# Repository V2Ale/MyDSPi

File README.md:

<!DOCTYPE html PUBLIC "-//W3C//DTD HTML 4.01//EN" "http://www.w3.org/TR/html4/strict.dtd">
<html>
<head>
  <meta content="text/html; charset=ISO-8859-1"
 http-equiv="content-type">
  <h1>MyDSPi</h1>
</head>
<body>

<br>
<div style="margin-left: 40px;">MyDSPi is an easy to
implement solution for audio processing and amplification with a
Raspberry Pi (2 and 3) audio output. <br>
It's intended to be a cost effective solution to make
active&nbsp;speakers.<br>
Electronic circuit is based on Analog Device ADAU1701 DSP and Texas
Instrument TPA3118 amplifier.<br>
<br>
More information  avaialble at <a href="http://mydspi;v2ale.com/?utm_source=Github&utm_medium=Link&utm_campaign=mainpage" >mydspi.v2ale.com</a>
<br>
</div>
<br style="font-weight: bold;">
<h3>Hardware description</h3>
<h4 style="margin-left: 40px; width: 1239px;">Overview : </h4>
<div style="margin-left: 40px;"><br>
<div style="margin-left: 40px;">MyDSPi is designed to be
compact and mounted over a Raspberry Pi 2 board. Hardware is split over
2 printed circuit boards stack one above the other.<br><br>
<br>
<br>
The first board is dedicated to DSP processing and Digital to Analog
signal convertion from Raspberry Pi audio output.&nbsp;Audio must
be output from Raspberry
Pi through I2S output pins.<br>
DSP is controlled by Raspberry Pi using I2C&nbsp; interface and
requires no
advanced DSP programming to have signal processed and can be easily
configured by editing a configuration file.<br>
The DSP work at fixed sampling frequency of 48000 Hz. <br>
Output channels are transmitted to the amplifier board through I2S
protocol.<br>
<br>
The second board host Digital to Analog converter that feed the
amplifier with analog signal for amplification. Power supply input
circuit is also located on this PCB, which can accept any supply
voltage from 12 to 24 volts to feed all system power supply (including
the Raspberry Pi).<br>
<br>
For more details about each board, please refer to :<br><br>
<ul>
<li><a href="https://github.com/V2Ale/MyDSPi/tree/master/Electronic/DSP%20Board/2.0">DSP Board page</a></li>
<li><a href="https://github.com/V2Ale/MyDSPi/tree/master/Electronic/Amplification%20Board">Amplifier board page</a></li>
</ul>
</div>
</div>
<br>
<h3><big>Software description</big></h3>
<div style="margin-left: 40px;">Once install is done the
MyDSPi software run at start-up to load default DSP parameters and then
load the parameters read from the configuration file.<br>
<br>
</div>
<h4>DSP Capabilities description</h4>
<br>
<div style="margin-left: 80px;">The default parameters of
the DSP are right now a 2 input / 2
output configuration with a default crossover and no EQ values loaded.
Parameter customization is done throught the MyDSPi.conf file and can
configure : <br>
<br>
<div style="margin-left: 40px;">- Input channels volume
controls<br>
- Input channels mute controls<br>
- 2 channels crossover<br>
- output channels Delay (up to 412 samples) <br>
- Ouput channel mute control<br>
- Ouput channel phase control<br>
- Output channel volume control<br>
</div>
</div>
<br>
<h3>Installation</h3>
Installation of &nbsp;MyDSPi is tested and developped for Linux
Raspbian Jessie distribution.<br>
<br>
The following step describes only the installation major steps. <br>

<ul>
<li>Setup I2C (<a href="https://learn.adafruit.com/adafruits-raspberry-pi-lesson-4-gpio-setup/configuring-i2c">
https://learn.adafruit.com/adafruits-raspberry-pi-lesson-4-gpio-setup/configuring-i2c</a>)<br>
</li>
<li>Setup I2S soundcard (following &nbsp;<a href="https://www.hifiberry.com/build/documentation/hifiberry-software-configuration/">https://www.hifiberry.com/build/documentation/hifiberry-software-configuration/</a>)<br>
</li>
<li>
 Run installation script (see https://github.com/V2Ale/MyDSPi/tree/master/Software/Install)<br>
 </li>
 </ul>

<h3>Configuration</h3>
To edit the configuration file, use the command :<br>
<pre>&nbsp;sudo nano /etc/default/MyDSPi.conf</pre>
For more details about configuration file rules, please refer to <span
 style="color: red;">https://github.com/V2Ale/MyDSPi/tree/master/Software/Install/config</span><br>
<br>
<h3>Roadmap</h3>
Support 5.1 configuration<br>
Support 7.1 configuration<br>
Support quadriphonic configuration<br>
&nbsp;<br>

</body>
</html>

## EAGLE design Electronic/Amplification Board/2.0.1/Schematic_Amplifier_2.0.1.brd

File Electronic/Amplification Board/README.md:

<!DOCTYPE html PUBLIC "-//W3C//DTD HTML 4.01//EN" "http://www.w3.org/TR/html4/strict.dtd">
<html>
<head>
  <meta content="text/html; charset=ISO-8859-1"
 http-equiv="content-type">
</head>
<body>
<h1>Amplifier and Power Supply Board</h1>
<h3>Overview</h3>
<br>
Amplifier and Power Supply board is the second PCB of this project that
can be stack with the DSP board. It's designed to host 2 set of
amplifiers and DAC, which can handle up to for 4 channels of
amplification. In addition, the board is used for power supply the
entire stack. <br>
<br style="color: red;">
<span style="color: red;"></span><br>
<br>
<h3>DAC</h3>
<br>
Digital to Analog conveters used for this board are PCM5102a (and
similar such as PCM5100). The
benefit of using PCM5102 DAC is that it does not requires the I2S
high frequency system clock (SCK) to work making routing between boards
much easier. <br>
Also, this component provides additionnal controls like demphasis, FIR
or IIR filter of output, format (I2S or Left justified) and soft mute.
Those controls are driven by a port expander with I2C interface that
allows end user to use this amplifier board for other designs. More
details on those controls can be found in the component datasheet. <br>
Last, this component
is readily cheap and available on the market (PCM5100 being pin to pin
compatible).<br>
<br>
<br>
<h3>Amplifier</h3>
&nbsp;<br>
The Texas Instrument TPA3118 amplifiers are stereo class D amplifiers
that can drive 2x30W into 8 Ohms load (with a 24V supply). It can
operate with a wide single operating voltage from 4.5V to 26V keeping
the power supply design simple. <br>
As audio input, the amplifier expect single ended audio which are
provided by DAC. All external controls (like gain) of the amplifier are
set constant except the amplifier mute which can be controlled thanks
to the port expander.<br>
Last, the amplifier integrates bad operating conditions (like
overtemperature, output short circuit) which are sent back to the
Faultz pins. Those pins are connected to the port expander and can be
monitored as well.<br>
<br>
<h3>Port Expander</h3>
<br>
As explain in previous parts, the port expander is in charge of
monitoring amplifier state and set DAC and amplifiers controls. The
part used for this task is very common MCP23008 from Microchip.<br>
<br>
<h3>Power Supply </h3>
<br>
The board do not have any power supply transformer and switch mode
power supply block design is outside the scope of this project. As a
result, a maximum of 26V voltage is expected at the DC jack terminal
connector. This voltage is directly used to feed the amplifiers and is
also converted down to a 5V supply voltage for all other boards
(including Raspberry Pi supply). &nbsp; <br>
<br>
<h3>Connectors </h3>
<br>
The&nbsp; 40 pin connector is used to connected to the DSP board
and get DSP output channels,&nbsp; I2C and amplifier mute command.
It also provides the supply rail voltage for the entire project.<br>
<br>
<span style="color: red;">[IMAGE DU SCHEMA DU CONNETEUR]</span><br>
<br>
<table style="text-align: left; width: 378px; height: 1216px;"
 border="1" cellpadding="2" cellspacing="2">
  <tbody>
    <tr>
      <td>Pin</td>
      <td>Name &nbsp; &nbsp; </td>
      <td>Description &nbsp; &nbsp; &nbsp; &nbsp;
&nbsp;</td>
    </tr>
    <tr>
      <td>1</td>
      <td>DC In</td>
      <td>Input Power supply is duplicated on this pin</td>
    </tr>
    <tr>
      <td>2</td>
      <td>DC In</td>
      <td>Input Power supply is duplicated on this pin</td>
    </tr>
    <tr>
      <td>3</td>
      <td>-</td>
      <td>Not used</td>
    </tr>
    <tr>
      <td>4</td>
      <td>SCL</td>
      <td>I2C Clock</td>
    </tr>
    <tr>
      <td>5</td>
      <td>-</td>
      <td>Not used</td>
    </tr>
    <tr>
      <td>6</td>
      <td>SDA</td>
      <td>I2C Data</td>
    </tr>
    <tr>
      <td>7</td>
      <td>Amp_mute</td>
      <td>Pin connected to Raspberry pi and amplifier mute pin.</td>
    </tr>
    <tr>
      <td>8</td>
      <td>-</td>
      <td>Not used</td>
    </tr>
    <tr>
      <td>9</td>
      <td>-</td>
      <td>Not used</td>
    </tr>
    <tr>
      <td>10</td>
      <td>-</td>
      <td>Not used</td>
    </tr>
    <tr>
      <td>11</td>
      <td>GND</td>
      <td>Ground</td>
    </tr>
    <tr>
      <td>12</td>
      <td>-</td>
      <td>Not used</td>
    </tr>
    <tr>
      <td>13</td>
      <td>-</td>
      <td>Not used</td>
    </tr>
    <tr>
      <td>14</td>
      <td>-</td>
      <td>Not used</td>
    </tr>
    <tr>
      <td>15</td>
      <td>-</td>
      <td>Not used</td>
    </tr>
    <tr>
      <td>16</td>
      <td>-</td>
      <td>Not used</td>
    </tr>
    <tr>
      <td>17</td>
      <td>GPO3</td>
      <td>DSP MPIO3 Output pin</td>
    </tr>
    <tr>
      <td>18</td>
      <td>GPO2</td>
      <td>DSP&nbsp;MPIO2 Output pin</td>
    </tr>
    <tr>
      <td>19</td>
      <td>GPO1</td>
      <td>DSP&nbsp;MPIO1 Output pin</td>
    </tr>
    <tr>
      <td>20</td>
      <td>DSPIN_SADATA0</td>
      <td>DSP I2S input pin 1</td>
    </tr>
    <tr>
      <td>21</td>
      <td>DSP_SDATA0</td>
      <td>DSP I2S output pin 1</td>
    </tr>
    <tr>
      <td>22</td>
      <td>DSP_BCK</td>
      <td>DSP I2S Bitclock output</td>
    </tr>
    <tr>
      <td>23</td>
      <td>DSP_SDATA1</td>
      <td>DSP I2S output pin 2</td>
    </tr>
    <tr>
      <td>24</td>
      <td>DSP_LRCK</td>
      <td>DSP I2S Bitclock output</td>
    </tr>
    <tr>
      <td>25</td>
      <td>ANALOG_IN_R</td>
      <td>DSP Analog input pin 1</td>
    </tr>
    <tr>
      <td>26</td>
      <td>ANALOG_IN_L</td>
      <td>DSP Analog input pin 2</td>
    </tr>
    <tr>
      <td>27</td>
      <td>AUDIO_OUT0</td>
      <td>DSP Analog output 1</td>
    </tr>
    <tr>
      <td>28</td>
      <td>GPO9</td>
      <td>DSP MPIO 9</td>
    </tr>
    <tr>
      <td>29</td>
      <td>AUDIO_OUT1</td>
      <td>DSP Analog output 2</td>
    </tr>
    <tr>
      <td>30</td>
      <td>GPO8</td>
      <td>DSP MPIO 8</td>
    </tr>
    <tr>
      <td>31</td>
      <td>AUDIO_OUT2</td>
      <td>DSP Analog output 3</td>
    </tr>
    <tr>
      <td>32</td>
      <td>AUDIO_OUT3</td>
      <td>DSP Analog output 4</td>
    </tr>
    <tr>
      <td>33</td>
      <td>-</td>
      <td>Not used</td>
    </tr>
    <tr>
      <td>34</td>
      <td>-</td>
      <td>Not used</td>
    </tr>
    <tr>
      <td>35</td>
      <td>GND</td>
      <td>Ground</td>
    </tr>
    <tr>
      <td>36</td>
      <td>GND</td>
      <td>Ground</td>
    </tr>
    <tr>
      <td>37</td>
      <td>5V</td>
      <td>5V power supply</td>
    </tr>
    <tr>
      <td>38</td>
      <td>GND</td>
      <td>Ground</td>
    </tr>
    <tr>
      <td>39</td>
      <td>5V</td>
      <td>5V power supply</td>
    </tr>
    <tr>
      <td>40</td>
      <td>5V</td>
      <td>5V power supply</td>
    </tr>
  </tbody>
</table>
<br>
<br>
</body>
</html>

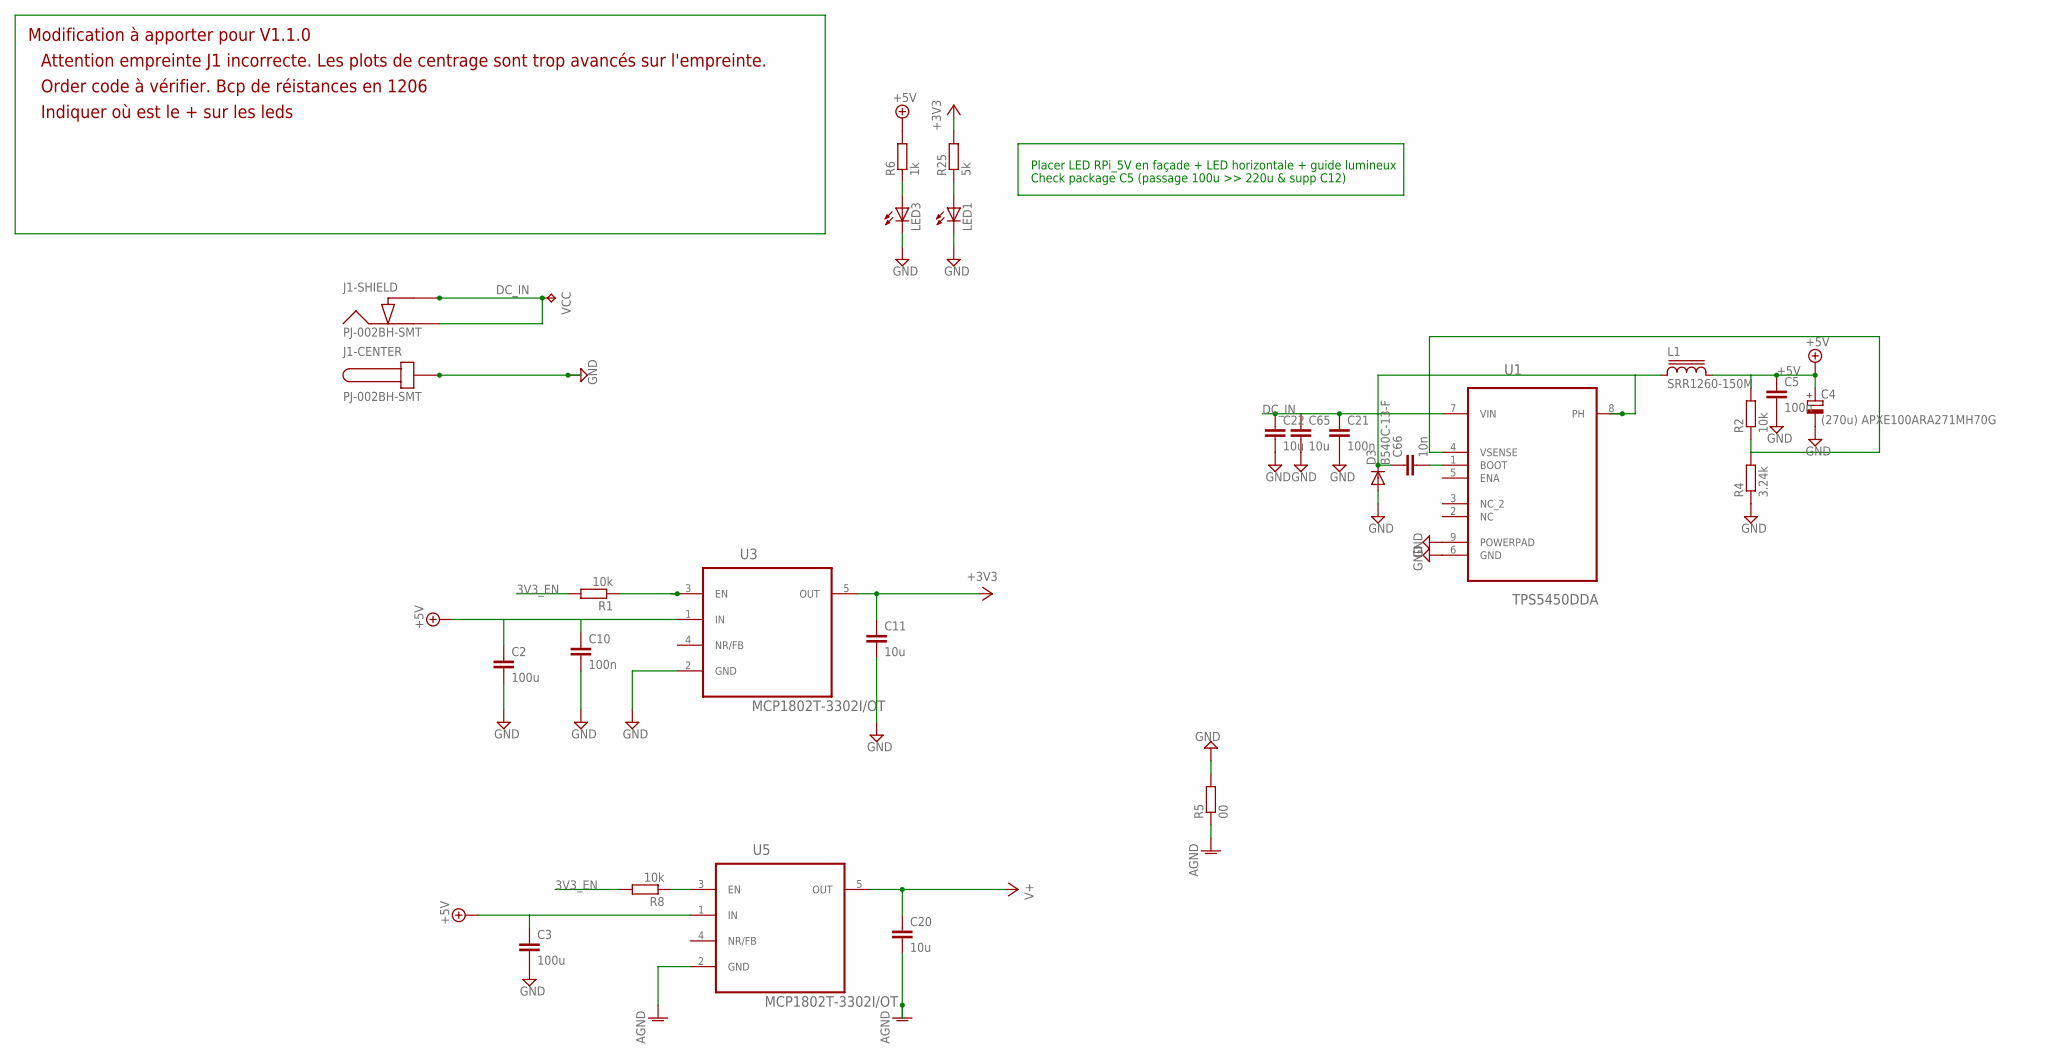
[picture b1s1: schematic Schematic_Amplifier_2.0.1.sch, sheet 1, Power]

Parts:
C2, C3: 100u; C1206
C4: (270u) APXE100ARA271MH70G; 175TMP-0810
C5, C10, C21: 100n; C0603
C11, C20, C22, C65: 10u; C0805
C66: 10n; C0603
D3: B540C-13-F; SMC
J1: PJ-002BH-SMT; 002BH-SMT
L1: SRR1260-150M; SRR1280
LED1: LEDSML0603; SML0603
LED3: LEDSML1206; SML1206
R1, R2, R8: 10k; R0603
R4: 3.24k; R0603
R5: 00; R0603
R6: 1k; R0603
R25: 5k; R0603
U1: TPS5450DDA; SOIC127P600X170-9N
U3, U5: MCP1802T-3302I/OT; SOT95P280X145-5N
VCC: TPTP20R; TP20R

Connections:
3V3_EN: R1.2, R8.2; also elsewhere on the board
+3V3: C11.1, R25.2, U3.5 (OUT); also elsewhere on the board
+5V: C2.1, C3.1, C4.+, C5.1, C10.1, L1.2, R2.2, R6.2, U3.1 (IN), U5.1 (IN); also elsewhere on the board
AGND: C20.2, R5.1, U5.2 (GND); also elsewhere on the board
DC_IN: C21.1, C22.1, C65.1, J1.2, J1.3, U1.7 (VIN), VCC.TP; also elsewhere on the board
GND: C2.2, C3.2, C4.-, C5.2, C10.2, C11.2, C21.2, C22.2, C65.2, D3.A, J1.CENTER1 (1), J1.CENTER2 (1), LED1.C, LED3.C, R4.1, R5.2, U1.6 (GND), U1.9 (POWERPAD), U3.2 (GND); also elsewhere on the board
unnamed: R1.1, U3.3 (EN)
unnamed: LED1.A, R25.1
unnamed: C66.2, U1.1 (BOOT)
unnamed: LED3.A, R6.1
unnamed: R8.1, U5.3 (EN)
unnamed: C66.1, D3.C, L1.1, U1.8 (PH)
unnamed: R2.1, R4.2, U1.4 (VSENSE)
V+: C20.1, U5.5 (OUT); also elsewhere on the board

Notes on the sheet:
Placer LED RPi_5V en façade + LED horizontale + guide lumineux
Check package C5 (passage 100u >> 220u & supp C12)
Attention empreinte J1 incorrecte. Les plots de centrage sont trop avancés sur l'empreinte.
Modification à apporter pour V1.1.0
Order code à vérifier. Bcp de réistances en 1206
Indiquer où est le + sur les leds

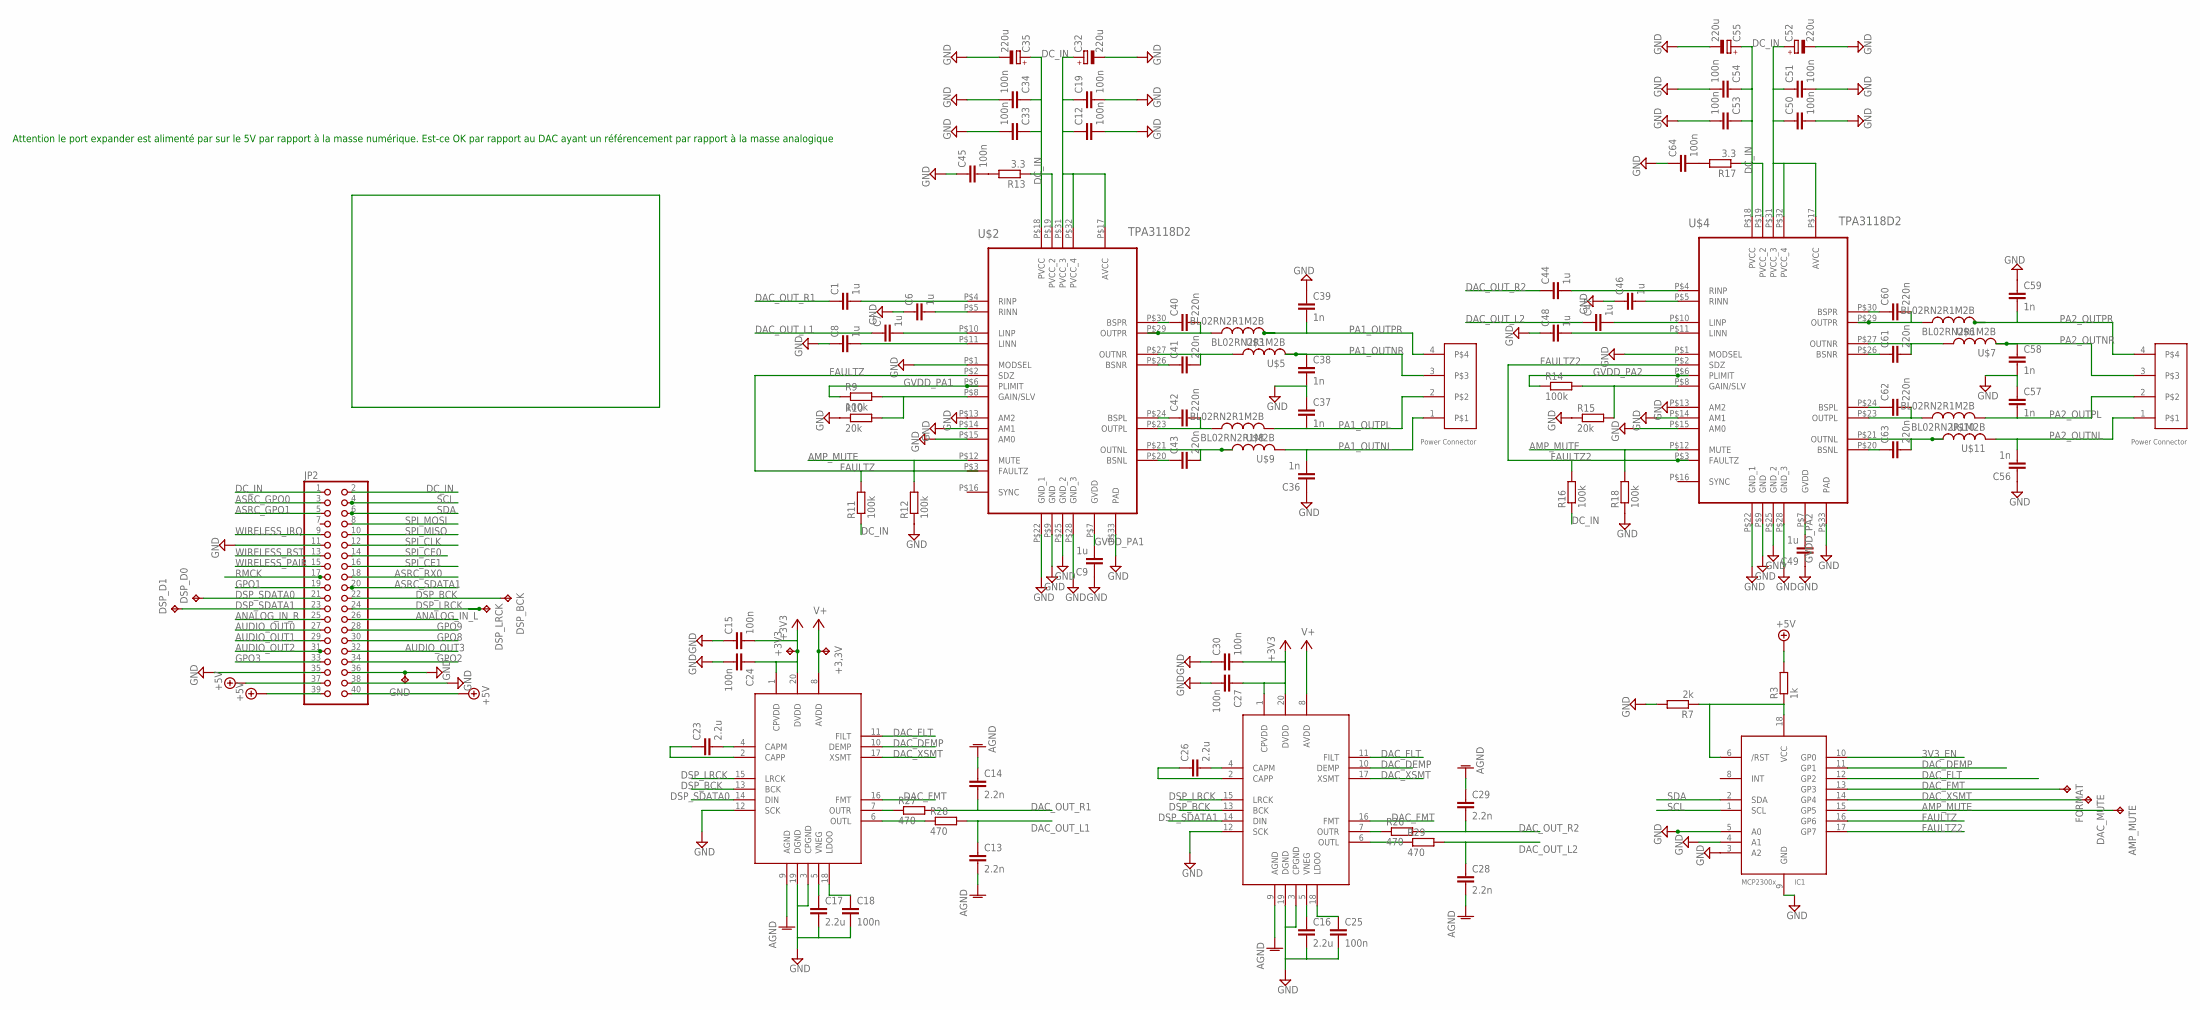
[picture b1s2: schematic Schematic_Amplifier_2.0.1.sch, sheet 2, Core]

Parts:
+3,3V, +3V3: TPTP10R; TP10R
AMP_MUTE: TPTP08R; TP08R
C1, C6, C7, C8, C9, C44, C46, C47, C48, C49: 1u; C0603
C12, C15, C18, C19, C24, C25, C27, C30, C33, C34, C45, C50, C51, C53, C54, C64: 100n; C0603
C13, C14, C28, C29: 2.2n; C0603
C16, C17, C23, C26: 2.2u; C0603
C32, C35, C52, C55: 220u; E2,5-6
C36, C37, C38, C39, C56, C57, C58, C59: 1n; C0603
C40, C41, C42, C43, C60, C61, C62, C63: 220n; C0603
DAC0, DAC1: PCM5102A; 20L-TSSOP
DAC_MUTE: TPTP08R; TP08R
DSP_BCK: TPTP08R; TP08R
DSP_D0, DSP_D1: TPTP08R; TP08R
DSP_LRCK: TPTP08R; TP08R
FORMAT: TPTP08R; TP08R
GND: TPTP19SQ; TP19SQ
IC1: MCP23008/SO; SO18W
JP2: PINHD-2X20; 2X20
R3: 1k; R0603
R7: 2k; R0603
R9, R11, R12, R14, R16, R18: 100k; R0603
R10, R15: 20k; R0603
R13, R17: 3.3; R0603
R26, R27, R28, R29: 470; R0603
U$1, U$12: 1-1123723-4; POWER_CON_HEADER
U$2, U$4: TPA3118D2; TSSOP32
U$3, U$5, U$6, U$7, U$8, U$9, U$10, U$11: BL02RN2R1M2B; FB

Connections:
3V3_EN: IC1.10 (GP0); also elsewhere on the board
$OUTR: DAC0.7 (OUTR), R26.1
+3V3: +3V3.TP, C15.2, C24.1, C27.1, C30.2, DAC0.1 (CPVDD), DAC0.20 (DVDD), DAC1.1 (CPVDD), DAC1.20 (DVDD); also elsewhere on the board
+5V: JP2.37, JP2.39, JP2.40, R3.2; also elsewhere on the board
AGND: C13.2, C14.1, C28.2, C29.1, DAC0.9 (AGND), DAC1.9 (AGND); also elsewhere on the board
AMP_MUTE: AMP_MUTE.TP, IC1.15 (GP5), R12.2, R18.2, U$2.P$12 (MUTE), U$4.P$12 (MUTE)
ANALOG_IN_L: JP2.26
ANALOG_IN_R: JP2.25
ASRC_GPO0: JP2.3
ASRC_GPO1: JP2.5
ASRC_RX0: JP2.18
ASRC_SDATA1: JP2.20
AUDIO_OUT0: JP2.27
AUDIO_OUT1: JP2.29
AUDIO_OUT2: JP2.31
AUDIO_OUT3: JP2.32
DAC_DEMP: DAC0.10 (DEMP), DAC1.10 (DEMP), IC1.11 (GP1)
DAC_FLT: DAC0.11 (FILT), DAC1.11 (FILT), IC1.12 (GP2)
DAC_FMT: DAC0.16 (FMT), DAC1.16 (FMT), FORMAT.TP, IC1.13 (GP3)
DAC_OUT_L1: C7.1, C13.1, R28.2
DAC_OUT_L2: C28.1, C47.1, R29.2
DAC_OUT_R1: C1.1, C14.2, R27.2
DAC_OUT_R2: C29.2, C44.1, R26.2
DAC_XSMT: DAC0.17 (XSMT), DAC1.17 (XSMT), DAC_MUTE.TP, IC1.14 (GP4)
DC_IN: C12.1, C19.1, C32.+, C33.1, C34.1, C35.+, C50.1, C51.1, C52.+, C53.1, C54.1, C55.+, JP2.1, JP2.2, R11.1, R13.1, R16.1, R17.1, U$2.P$17 (AVCC), U$2.P$18 (PVCC), U$2.P$31 (PVCC_3), U$2.P$32 (PVCC_4), U$4.P$17 (AVCC), U$4.P$18 (PVCC), U$4.P$31 (PVCC_3), U$4.P$32 (PVCC_4); also elsewhere on the board
DSP_BCK: DAC0.13 (BCK), DAC1.13 (BCK), DSP_BCK.TP, JP2.22
DSP_LRCK: DAC0.15 (LRCK), DAC1.15 (LRCK), DSP_LRCK.TP, JP2.24
DSP_SDATA0: DAC1.14 (DIN), DSP_D0.TP, JP2.21
DSP_SDATA1: DAC0.14 (DIN), DSP_D1.TP, JP2.23
FAULTZ: IC1.16 (GP6), R11.2, U$2.P$2 (SDZ), U$2.P$3 (FAULTZ)
FAULTZ2: IC1.17 (GP7), R16.2, U$4.P$2 (SDZ), U$4.P$3 (FAULTZ)
GND: C6.1, C8.1, C9.1, C12.2, C15.1, C16.2, C17.2, C18.2, C19.2, C24.2, C25.2, C27.2, C30.1, C32.-, C33.2, C34.2, C35.-, C36.1, C37.1, C38.2, C39.1, C45.1, C46.1, C48.1, C49.1, C50.2, C51.2, C52.-, C53.2, C54.2, C55.-, C56.1, C57.1, C58.2, C59.1, C64.1, DAC0.3 (CPGND), DAC0.12 (SCK), DAC0.19 (DGND), DAC1.3 (CPGND), DAC1.12 (SCK), DAC1.19 (DGND), GND.TP, IC1.3 (A2), IC1.4 (A1), IC1.5 (A0), IC1.9 (GND), JP2.11, JP2.35, JP2.36, JP2.38, R7.2, R10.1, R12.1, R15.1, R18.1, U$2.P$1 (MODSEL), U$2.P$9 (GND), U$2.P$13 (AM2), U$2.P$14 (AM1), U$2.P$15 (AM0), U$2.P$22 (GND_1), U$2.P$25 (GND_2), U$2.P$28 (GND_3), U$2.P$33 (PAD), U$4.P$1 (MODSEL), U$4.P$9 (GND), U$4.P$13 (AM2), U$4.P$14 (AM1), U$4.P$15 (AM0), U$4.P$22 (GND_1), U$4.P$25 (GND_2), U$4.P$28 (GND_3), U$4.P$33 (PAD); also elsewhere on the board
GPO1: JP2.19
GPO2: JP2.34
GPO3: JP2.33
GPO8: JP2.30
GPO9: JP2.28
GVDD_PA1: C9.2, R9.1, U$2.P$6 (PLIMIT), U$2.P$7 (GVDD)
GVDD_PA2: C49.2, R14.1, U$4.P$6 (PLIMIT), U$4.P$7 (GVDD)
unnamed: C1.2, U$2.P$4 (RINP)
unnamed: IC1.6 (/RST), IC1.18 (VCC), R3.1, R7.1
unnamed: C6.2, U$2.P$5 (RINN)
unnamed: C7.2, U$2.P$10 (LINP)
unnamed: C8.2, U$2.P$11 (LINN)
unnamed: R9.2, R10.2, U$2.P$8 (GAIN/SLV)
unnamed: C41.2, U$2.P$27 (OUTNR), U$5.P$1 (1)
unnamed: C40.2, U$2.P$29 (OUTPR), U$3.P$1 (1)
unnamed: C42.2, U$2.P$23 (OUTPL), U$8.P$1 (1)
unnamed: C43.2, U$2.P$21 (OUTNL), U$9.P$1 (1)
unnamed: C44.2, U$4.P$4 (RINP)
unnamed: C40.1, U$2.P$30 (BSPR)
unnamed: C17.1, DAC1.5 (VNEG)
unnamed: C23.2, DAC1.4 (CAPM)
unnamed: C45.2, R13.2
unnamed: C46.2, U$4.P$5 (RINN)
unnamed: C47.2, U$4.P$10 (LINP)
unnamed: C41.1, U$2.P$26 (BSNR)
unnamed: C42.1, U$2.P$24 (BSPL)
unnamed: C43.1, U$2.P$20 (BSNL)
unnamed: C48.2, U$4.P$11 (LINN)
unnamed: DAC1.7 (OUTR), R27.1
unnamed: DAC1.6 (OUTL), R28.1
unnamed: C16.1, DAC0.5 (VNEG)
unnamed: C25.1, DAC0.18 (LDOO)
unnamed: C26.2, DAC0.4 (CAPM)
unnamed: C18.1, DAC1.18 (LDOO)
unnamed: C26.1, DAC0.2 (CAPP)
unnamed: R14.2, R15.2, U$4.P$8 (GAIN/SLV)
unnamed: C23.1, DAC1.2 (CAPP)
unnamed: DAC0.6 (OUTL), R29.1
unnamed: C61.2, U$4.P$27 (OUTNR), U$7.P$1 (1)
unnamed: C60.2, U$4.P$29 (OUTPR), U$6.P$1 (1)
unnamed: C62.2, U$4.P$23 (OUTPL), U$10.P$1 (1)
unnamed: C63.2, U$4.P$21 (OUTNL), U$11.P$1 (1)
unnamed: C60.1, U$4.P$30 (BSPR)
unnamed: C61.1, U$4.P$26 (BSNR)
unnamed: C62.1, U$4.P$24 (BSPL)
unnamed: C63.1, U$4.P$20 (BSNL)
unnamed: C64.2, R17.2
PA1_OUTNL: C36.2, U$1.1, U$9.P$2 (2)
PA1_OUTNR: C38.1, U$1.3, U$5.P$2 (2)
PA1_OUTPL: C37.2, U$1.2, U$8.P$2 (2)
PA1_OUTPR: C39.2, U$1.4, U$3.P$2 (2)
PA2_OUTNL: C56.2, U$11.P$2 (2), U$12.1
PA2_OUTNR: C58.1, U$7.P$2 (2), U$12.3
PA2_OUTPL: C57.2, U$10.P$2 (2), U$12.2
PA2_OUTPR: C59.2, U$6.P$2 (2), U$12.4
RMCK: JP2.17
SCL: IC1.1 (SCL), JP2.4
SDA: IC1.2 (SDA), JP2.6
SPI_CE0: JP2.14
SPI_CE1: JP2.16
SPI_CLK: JP2.12
SPI_MISO: JP2.10
SPI_MOSI: JP2.8
V+: +3,3V.TP, DAC0.8 (AVDD), DAC1.8 (AVDD); also elsewhere on the board
WIRELESS_IRQ: JP2.9
WIRELESS_PAIR: JP2.15
WIRELESS_RST: JP2.13

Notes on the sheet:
Attention le port expander est alimenté par sur le 5V par rapport à la masse numérique. Est-ce OK par rapport au DAC ayant un référencement par rapport à la masse analogique

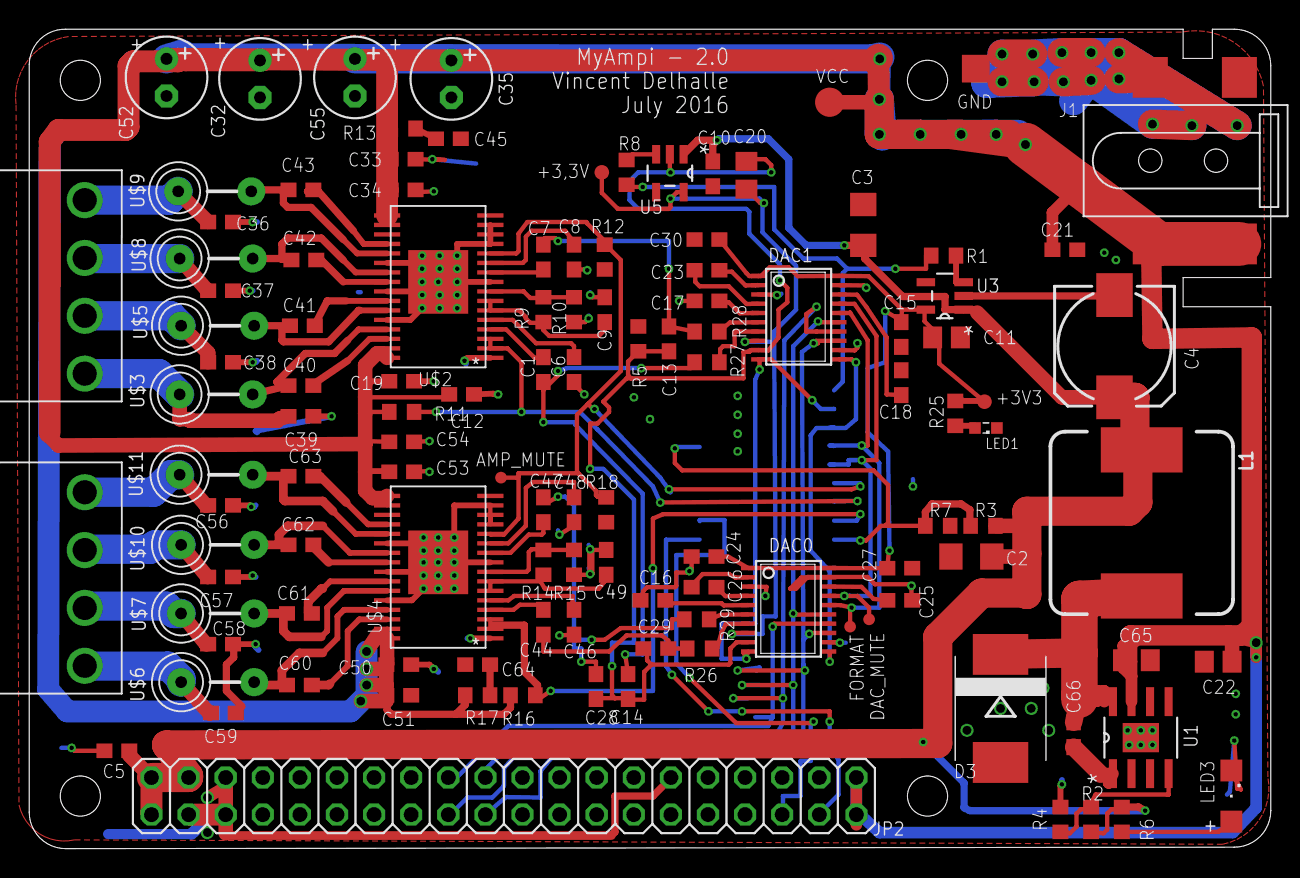
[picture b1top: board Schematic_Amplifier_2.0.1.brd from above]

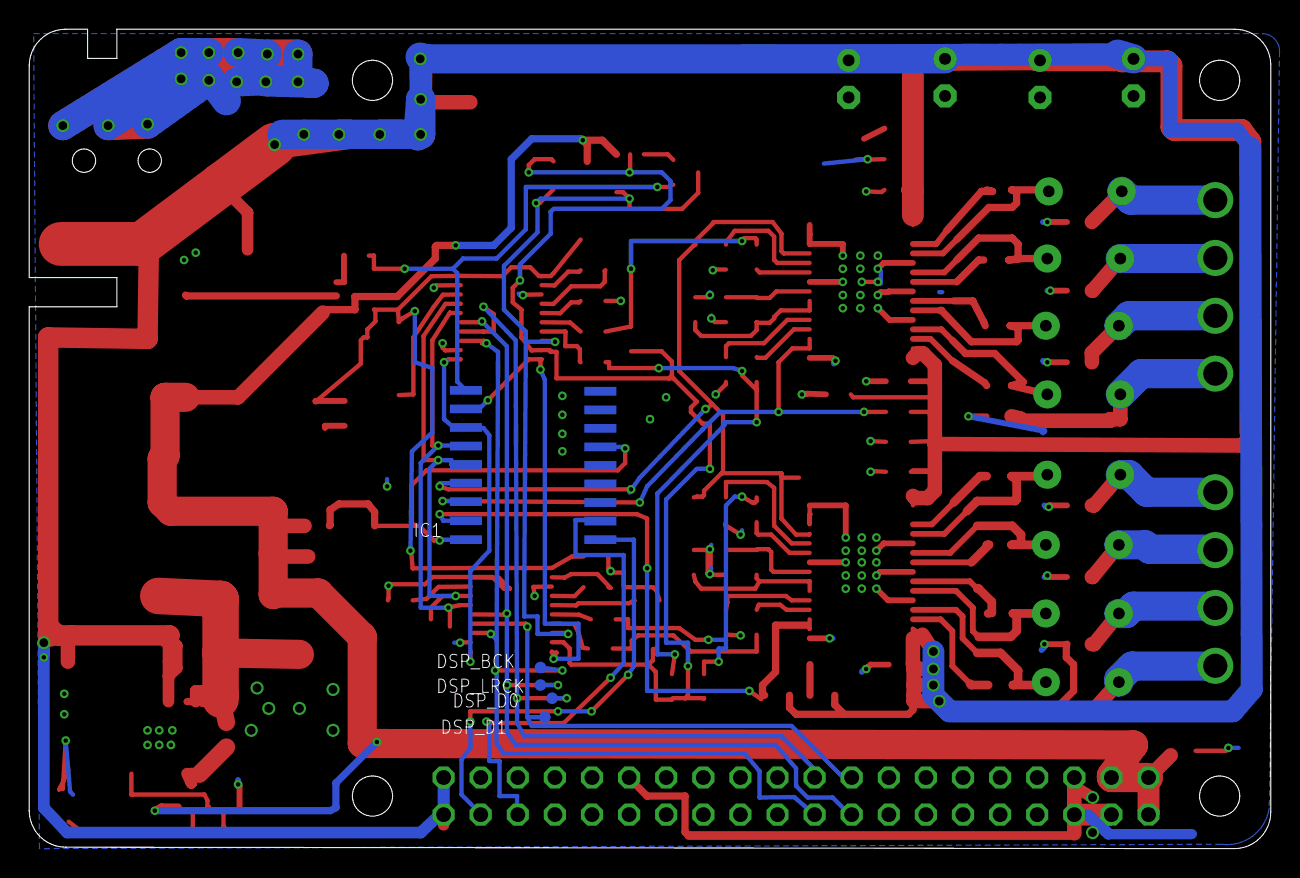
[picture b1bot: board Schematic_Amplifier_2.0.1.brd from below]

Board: 2 copper layers, 85.0 x 56.1 mm, 123 parts (5 on the bottom side), 82 nets.

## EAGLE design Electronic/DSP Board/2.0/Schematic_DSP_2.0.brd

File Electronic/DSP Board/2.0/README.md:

<!DOCTYPE html PUBLIC "-//W3C//DTD HTML 4.01//EN" "http://www.w3.org/TR/html4/strict.dtd">
<html>
<head>
  <meta content="text/html; charset=ISO-8859-1"
 http-equiv="content-type">
</head>
<body>
<h1>DSP PCB</h1>
<h3>Overview</h3>

The DSP used for this project is Analog Device's ADAU1701. It has many
input and output pins, either analog and digital. In the project scope,
this board in 2.0 version is limited to the use of 2 input to 8 digital
and 4 analog outputs.
<br>
It has two 40 pins connectors. One to connect this board to the
raspberry pi, the other to connect the board to other stages (like
amplifier &amp; power supply). The DSP clock is supplied by a
24.576 Mhz Quartz and the programming of the DSP is done via external
microcontroller (Raspberry Pi) using I2C interface.
<br><br>

<h3>Input channels</h3>
The DSP can process analog or digital (I2S) input, but only analog
input can be used. Despite the presence of analog input circuit
components routed in the 40 pin connecor, the project do not rely on
it. <br>
To use the board with the Raspberry Pi, the 3 wires of I2S are
converted by a DAC (PCM5102a) and provided to DSP by the analog input. <br>
The benefit of using PCM5102 DAC is that it does not requires the I2S
system clock (SCK) to work. It's especially useful because the
raspberry pi does not provide the SCK out of the box and it avoids
useless painful struggle with the kernel. <br>
Moreover, this component is readily cheap and available on the market
(PCM5100 being pin to pin compatible). Extra functionality of this DAC
such as filter type or soft mute are not used and not left to end user.<br>

<h3>Output channels</h3>
The DSP can output analog or digital (I2S) signals. Both of them are
available on this board but the amplifiers board is expecting I2S
signal before amplification stage. If you whish to use the I2S output
with other amplifier board, please mind that it does not output the SCK
as well. This choice has been made because the DAC do not need it to
operate normally and it avoid special care in the routing for this high
speed clock. <br>

<br><h3>I2S and clocks</h3>
Input and output I2S signals are working at fixed LRCK of 48kHz. The
DSP is driven by a 24.576MHz clock. I2S LRCK and BCK at input and
output of the DSP are connected together as required in the datasheet
of the component.<br>
It's not possible to run the DSP at other sampling frequency or with
different outside clock without changing the routing of the board. 
<br>
<br>
<h3>Connectors</h3>

The first 40 pin connector is fully compliant with the Raspberry Pi 2
and later connector layout. The other one, is used to provide input
&amp; output channels, power supply, I2C and amplifier mute to the
other stages.<br>
<br>
<span style="color: red;">[IMAGE DU SCHEMA DU CONNETEUR]</span><br>
<br>
<table style="text-align: left; width: 378px; height: 1216px;"
 border="1" cellpadding="2" cellspacing="2">
  <tbody>
    <tr>
      <td>Pin</td>
      <td>Name &nbsp; &nbsp; </td>
      <td>Description &nbsp; &nbsp; &nbsp; &nbsp;
&nbsp;</td>
    </tr>
    <tr>
      <td>1</td>
      <td>DC In</td>
      <td>Input Power supply is duplicated on this pin</td>
    </tr>
    <tr>
      <td>2</td>
      <td>DC In</td>
      <td>Input Power supply is duplicated on this pin</td>
    </tr>
    <tr>
      <td>3</td>
      <td>-</td>
      <td>Not used</td>
    </tr>
    <tr>
      <td>4</td>
      <td>SCL</td>
      <td>I2C Clock</td>
    </tr>
    <tr>
      <td>5</td>
      <td>-</td>
      <td>Not used</td>
    </tr>
    <tr>
      <td>6</td>
      <td>SDA</td>
      <td>I2C Data</td>
    </tr>
    <tr>
      <td>7</td>
      <td>Amp_mute</td>
      <td>Pin connected to Raspberry pi and amplifier mute pin.</td>
    </tr>
    <tr>
      <td>8</td>
      <td>-</td>
      <td>Not used</td>
    </tr>
    <tr>
      <td>9</td>
      <td>-</td>
      <td>Not used</td>
    </tr>
    <tr>
      <td>10</td>
      <td>-</td>
      <td>Not used</td>
    </tr>
    <tr>
      <td>11</td>
      <td>GND</td>
      <td>Ground</td>
    </tr>
    <tr>
      <td>12</td>
      <td>-</td>
      <td>Not used</td>
    </tr>
    <tr>
      <td>13</td>
      <td>-</td>
      <td>Not used</td>
    </tr>
    <tr>
      <td>14</td>
      <td>-</td>
      <td>Not used</td>
    </tr>
    <tr>
      <td>15</td>
      <td>-</td>
      <td>Not used</td>
    </tr>
    <tr>
      <td>16</td>
      <td>-</td>
      <td>Not used</td>
    </tr>
    <tr>
      <td>17</td>
      <td>GPO3</td>
      <td>DSP MPIO3 Output pin</td>
    </tr>
    <tr>
      <td>18</td>
      <td>GPO2</td>
      <td>DSP&nbsp;MPIO2 Output pin</td>
    </tr>
    <tr>
      <td>19</td>
      <td>GPO1</td>
      <td>DSP&nbsp;MPIO1 Output pin</td>
    </tr>
    <tr>
      <td>20</td>
      <td>DSPIN_SADATA0</td>
      <td>DSP I2S input pin 1</td>
    </tr>
    <tr>
      <td>21</td>
      <td>DSP_SDATA0</td>
      <td>DSP I2S output pin 1</td>
    </tr>
    <tr>
      <td>22</td>
      <td>DSP_BCK</td>
      <td>DSP I2S Bitclock output</td>
    </tr>
    <tr>
      <td>23</td>
      <td>DSP_SDATA1</td>
      <td>DSP I2S output pin 2</td>
    </tr>
    <tr>
      <td>24</td>
      <td>DSP_LRCK</td>
      <td>DSP I2S Bitclock output</td>
    </tr>
    <tr>
      <td>25</td>
      <td>ANALOG_IN_R</td>
      <td>DSP Analog input pin 1</td>
    </tr>
    <tr>
      <td>26</td>
      <td>ANALOG_IN_L</td>
      <td>DSP Analog input pin 2</td>
    </tr>
    <tr>
      <td>27</td>
      <td>AUDIO_OUT0</td>
      <td>DSP Analog output 1</td>
    </tr>
    <tr>
      <td>28</td>
      <td>GPO9</td>
      <td>DSP MPIO 9</td>
    </tr>
    <tr>
      <td>29</td>
      <td>AUDIO_OUT1</td>
      <td>DSP Analog output 2</td>
    </tr>
    <tr>
      <td>30</td>
      <td>GPO8</td>
      <td>DSP MPIO 8</td>
    </tr>
    <tr>
      <td>31</td>
      <td>AUDIO_OUT2</td>
      <td>DSP Analog output 3</td>
    </tr>
    <tr>
      <td>32</td>
      <td>AUDIO_OUT3</td>
      <td>DSP Analog output 4</td>
    </tr>
    <tr>
      <td>33</td>
      <td>-</td>
      <td>Not used</td>
    </tr>
    <tr>
      <td>34</td>
      <td>-</td>
      <td>Not used</td>
    </tr>
    <tr>
      <td>35</td>
      <td>GND</td>
      <td>Ground</td>
    </tr>
    <tr>
      <td>36</td>
      <td>GND</td>
      <td>Ground</td>
    </tr>
    <tr>
      <td>37</td>
      <td>5V</td>
      <td>5V power supply</td>
    </tr>
    <tr>
      <td>38</td>
      <td>GND</td>
      <td>Ground</td>
    </tr>
    <tr>
      <td>39</td>
      <td>5V</td>
      <td>5V power supply</td>
    </tr>
    <tr>
      <td>40</td>
      <td>5V</td>
      <td>5V power supply</td>
    </tr>
  </tbody>
</table>

<br>
<h3>Power Supply</h3>

The PCB receives its power supply from the amplifier PCB which has the
input DC jack socket and DC converters.<br>
The
5V supply at input&nbsp; is shared with the Raspberry Pi. From this
5V supply,
a 3.3V regulator on the board feed all components of this board.
</body>
</html>

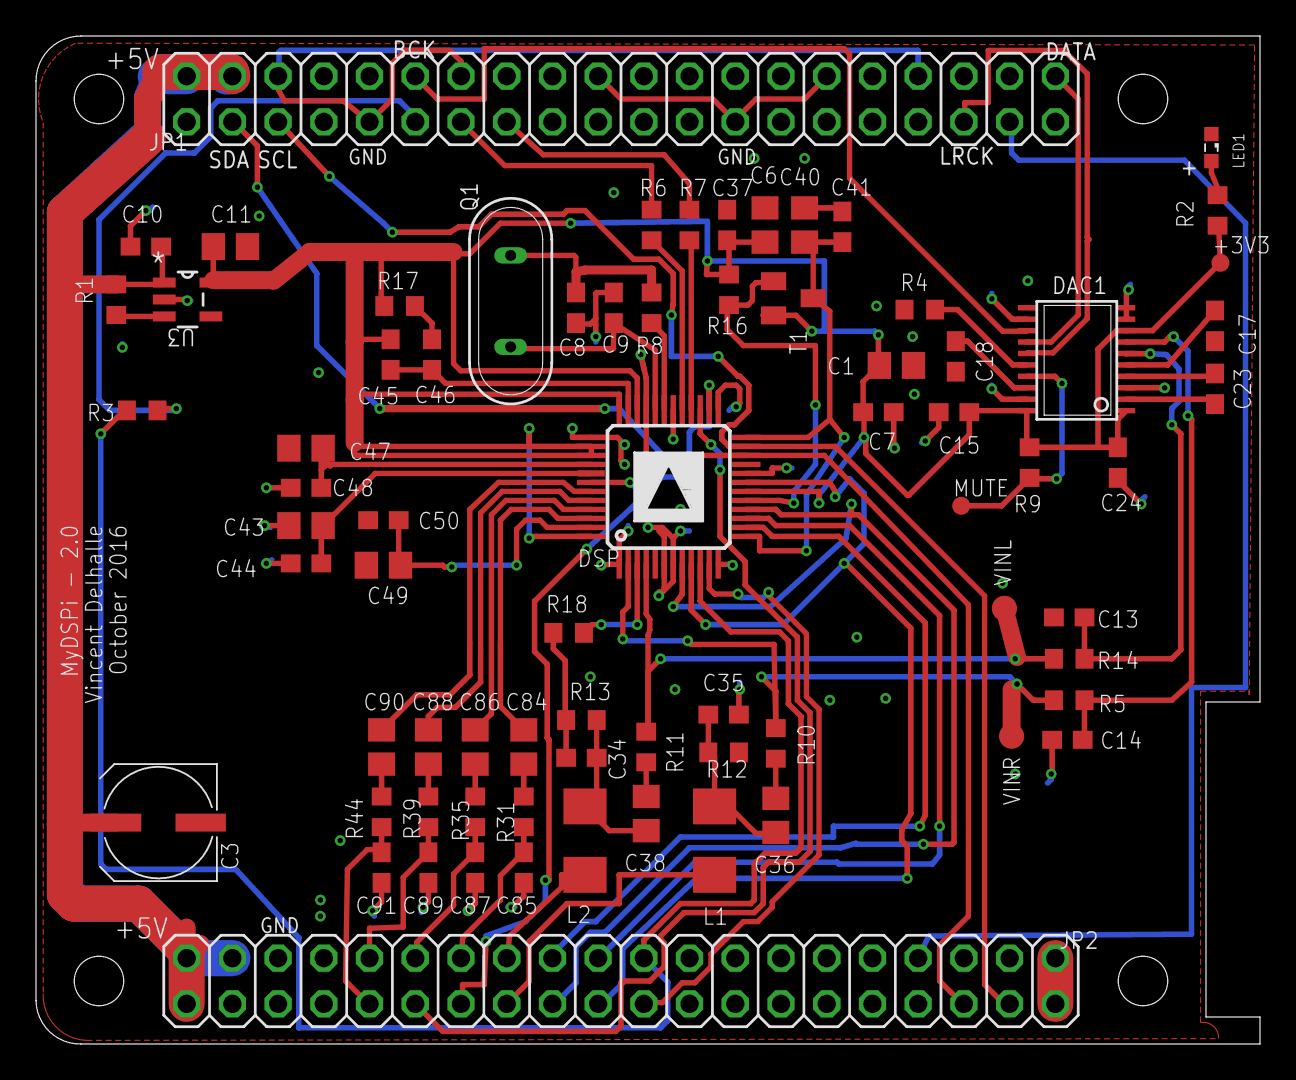
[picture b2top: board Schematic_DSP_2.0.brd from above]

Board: 2 copper layers, 68.0 x 56.0 mm, 73 parts (0 on the bottom side), 65 nets.

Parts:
+3V3: TPTP10R; TP10R
C1, C6, C11, C36, C38, C40, C43, C49: 10u; C0805
C3: UUR1A221MCL6GS; UD-6,3X7,7_NICHICON
C7, C10, C15, C18, C24, C37, C41, C44, C48, C50: 100n; C0603
C8, C9: 18p; C0603
C13, C14: 2.2n; C0603
C17, C23: 2.2u; C0603
C34, C35: 100p; C0603
C45: 3.3n; C0603
C46: 56n; C0603
C47, C84, C86, C88, C90: 47u; C0805
C85, C87, C89, C91: 5.6n; C0603
DAC1: PCM5102A; 20L-TSSOP
DSP: ADAU1701; PQFP48
JP1: Ebay:newdeparture2010; 2X20
JP2: 2X20
L1, L2: BLM41PG471SN1L; L4532M
LED1: SML0603
MUTE: TPTP10R; TP10R
Q1: 815-ABL-24.576-B2F; QS
R1: 10k; R0603
R2, R31, R35, R39, R44: 560; R0603
R3, R6, R7: {0}; R0603
R4, R9: 0; R0603
R5, R14: 18k 1%; R0603
R8: 100; R0603
R10, R11: {8k}; R0603
R12, R13: 49k9; R0603
R16: 1k; R0603
R17: 475R; R0603
R18: 18k; R0603
T1: ZXTP25040DFHTA; SOT23-BEC
U3: MCP1802T-3302I/OT; SOT95P280X145-5N
VINL: TPTP14R; TP14R
VINR: TPTP14R; TP14R

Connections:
3V3_EN: R1.1, U3.3
+3V3: +3V3.TP, C1.1, C6.1, C7.2, C11.1, C15.2, C24.1, C37.2, C45.1, DAC1.1, DAC1.8, DAC1.20, DSP.18, DSP.34, DSP.36, DSP.38, DSP.39, DSP.48, R2.2, R9.2, R16.2, R17.1, T1.E, U3.5
+5V: C3.+, C10.1, JP1.2, JP1.4, JP2.37, JP2.39, JP2.40, R1.2, U3.1
AMP_MUTE: JP1.37, JP2.7
ANALOG_IN_L: JP2.26, L1.1
ANALOG_IN_R: JP2.25, L2.1
AUDIO_OUT0: C85.2, JP2.27, R31.1
AUDIO_OUT1: C87.2, JP2.29, R35.1
AUDIO_OUT2: C89.2, JP2.31, R39.1
AUDIO_OUT3: C91.2, JP2.32, R44.1
CM: C47.1, C48.2, DSP.40
DAC_FMT: DAC1.16, R4.1
DAC_OUT0: C84.1, DSP.46
DAC_OUT1: C86.1, DSP.45
DAC_OUT2: C88.1, DSP.44
DAC_OUT3: C90.1, DSP.43
DAC_OUTL: C13.1, DAC1.6, R14.1
DAC_OUTR: C14.2, DAC1.7, R5.1
DAC_XSMT: DAC1.17, MUTE.TP, R9.1
DC_IN: JP2.1, JP2.2
DSPIN_SDATA0: DSP.11, JP2.20
DSP_BCK: DSP.9, DSP.19, JP2.22
DSP_LRCK: DSP.8, DSP.16, JP2.24
DSP_SDATA0: DSP.15, JP2.21
DSP_SDATA1: DSP.14, JP2.23
DSP_VINL: DSP.4, R11.2, R14.2, VINL.TP
DSP_VINR: DSP.2, R5.2, R10.2, VINR.TP
FILTA: C49.1, C50.2, DSP.47
FILTD: C43.1, C44.2, DSP.41
GND: C1.2, C3.-, C6.2, C7.1, C8.1, C9.1, C10.2, C11.2, C13.2, C14.1, C15.1, C17.2, C18.2, C24.2, C34.2, C35.2, C37.1, C40.2, C41.2, C43.2, C44.1, C47.2, C48.1, C49.2, C50.1, C85.1, C87.1, C89.1, C91.1, DAC1.3, DAC1.9, DAC1.10, DAC1.11, DAC1.12, DAC1.19, DSP.1, DSP.6, DSP.7, DSP.12, DSP.20, DSP.25, DSP.30, DSP.33, DSP.37, DSP.42, JP1.6, JP1.9, JP1.14, JP1.20, JP1.25, JP1.30, JP1.34, JP1.39, JP2.11, JP2.35, JP2.36, JP2.38, LED1.C, R4.2, R12.2, R13.2, R18.2, U3.2
GPO1: DSP.10, JP2.19, R3.2
GPO2: DSP.29, R6.2
GPO3: DSP.28, R7.2
GPO8: DSP.27, JP2.30
GPO9: DSP.26, JP2.28
MLCKI: C9.2, DSP.32, Q1.1
unnamed: LED1.A, R2.1
unnamed: C40.1, C41.1, DSP.13, DSP.24, T1.C
unnamed: DSP.31, R8.1
unnamed: DSP.17, R16.1, T1.B
unnamed: C8.2, Q1.2, R8.2
unnamed: C46.2, R17.2
unnamed: C17.1, DAC1.5
unnamed: C23.2, DAC1.4
unnamed: DSP.3, R18.1
unnamed: C36.2, R10.1
unnamed: C18.1, DAC1.18
unnamed: C38.2, R11.1
unnamed: C23.1, DAC1.2
unnamed: C34.1, C38.1, L2.2, R13.1
unnamed: C35.1, C36.1, L1.2, R12.1
unnamed: C84.2, R31.2
unnamed: C86.2, R35.2
unnamed: C88.2, R39.2
unnamed: C90.2, R44.2
PLL_LF: C45.2, C46.1, DSP.35
RPI_3V3: JP1.1, JP1.17
RPI_BCK: DAC1.13, JP1.12
RPI_GPIO17: JP1.11, R3.1
RPI_GPIO22: JP1.15, R7.1
RPI_GPIO27: JP1.13, R6.1
RPI_LRCK: DAC1.15, JP1.35
RPI_SDATA: DAC1.14, JP1.40
SCL: DSP.23, JP1.5, JP2.4
SDA: DSP.22, JP1.3, JP2.6

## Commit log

2017-06-17 Electronic part first commit
2017-06-17 software first commit
2017-06-17 update executable to install
2017-06-17 amplification board
2017-06-17 Elecrow config files
2017-06-17 Eagle lib folder
2017-06-23 change install script
2017-06-25 major changes of libini
2017-06-25 change MyDSPi.conf file
2017-06-25 Update install script
2017-07-26 Update roadmap
2017-07-26 Change readme to md

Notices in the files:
parts and their libraries:
volks73-cui: Creative Commons Attribution-ShareAlike 3.0 Unported (CC BY-SA 3.0), http://creativecommons.org/licenses/by-sa/3.0/.
Bourns - inductor: Copyright (C) 2008, Bob Starr
